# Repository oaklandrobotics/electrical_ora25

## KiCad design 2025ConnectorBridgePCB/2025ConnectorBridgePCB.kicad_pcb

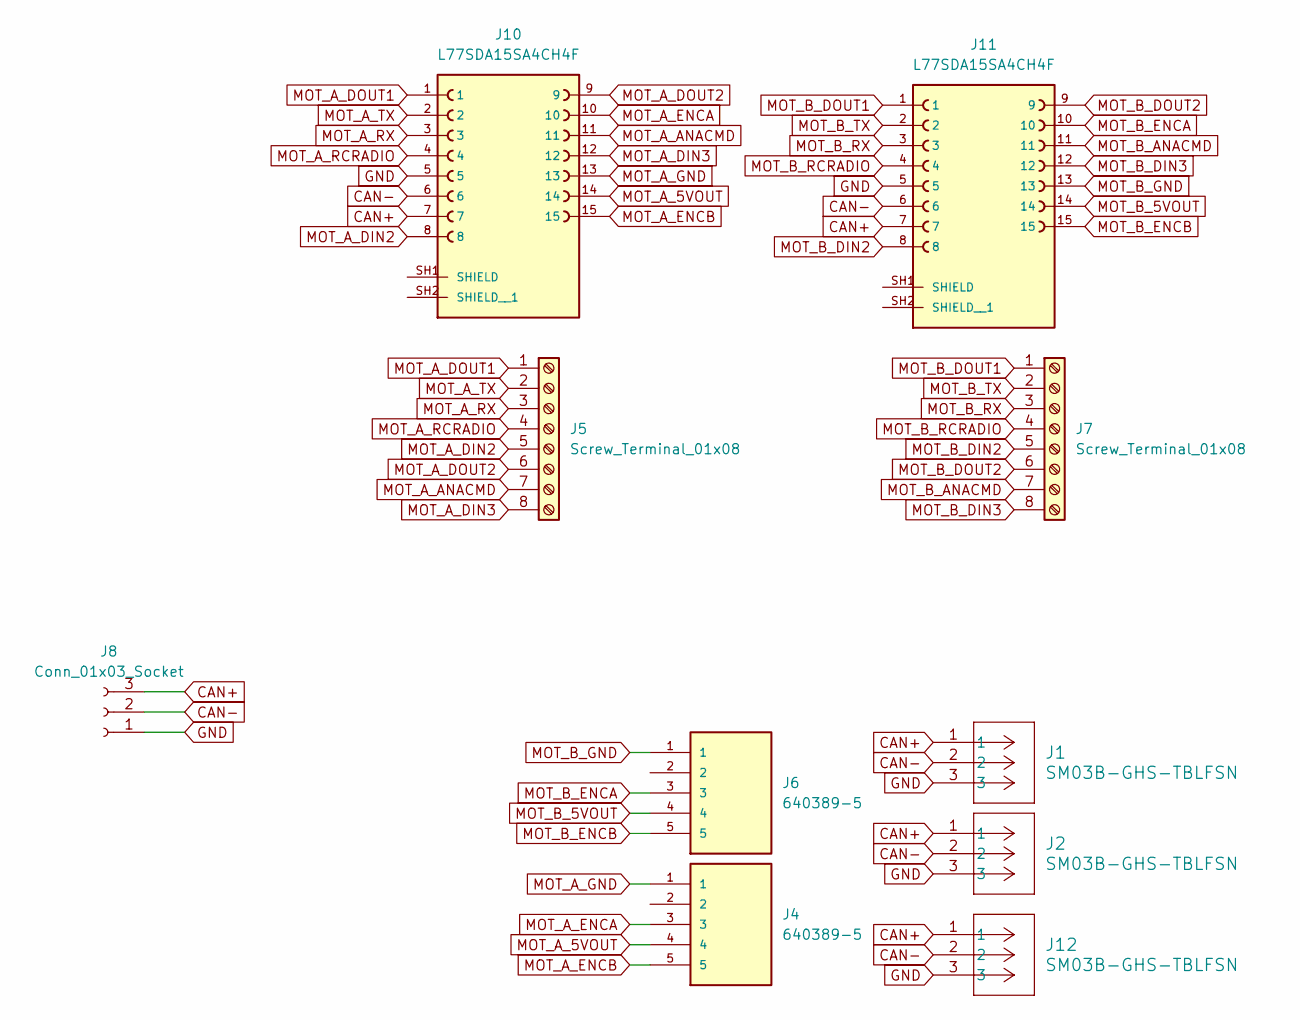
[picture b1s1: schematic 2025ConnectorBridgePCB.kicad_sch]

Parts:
J1, J2, J12: SM03B-GHS-TBLFSN; CONN_SM03B-GHS-TBLFSN_JST
J4, J6: 640389-5; TE_640389-5; PARTREV R; DigiKey_Part_Number A19921-ND
J5, J7: Screw_Terminal_01x08; TerminalBlock_Phoenix_MKDS-1,5-8_1x08_P5.00mm_Horizontal
J8: Conn_01x03_Socket; SolderWire-0.25sqmm_1x03_P4.2mm_D0.65mm_OD1.7mm
J10, J11: L77SDA15SA4CH4F; AMPHENOL_L77SDA15SA4CH4F; PARTREV 3

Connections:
CAN+: J1.1, J2.1, J8.3, J10.7, J11.7, J12.1
CAN-: J1.2, J2.2, J8.2, J10.6, J11.6, J12.2
GND: J1.3, J2.3, J8.1, J10.5, J11.5, J12.3
MOT_A_5VOUT: J4.4, J10.14
MOT_A_ANACMD: J5.7, J10.11
MOT_A_DIN2: J5.5, J10.8
MOT_A_DIN3: J5.8, J10.12
MOT_A_DOUT1: J5.1, J10.1
MOT_A_DOUT2: J5.6, J10.9
MOT_A_ENCA: J4.3, J10.10
MOT_A_ENCB: J4.5, J10.15
MOT_A_GND: J4.1, J10.13
MOT_A_RCRADIO: J5.4, J10.4
MOT_A_RX: J5.3, J10.3
MOT_A_TX: J5.2, J10.2
MOT_B_5VOUT: J6.4, J11.14
MOT_B_ANACMD: J7.7, J11.11
MOT_B_DIN2: J7.5, J11.8
MOT_B_DIN3: J7.8, J11.12
MOT_B_DOUT1: J7.1, J11.1
MOT_B_DOUT2: J7.6, J11.9
MOT_B_ENCA: J6.3, J11.10
MOT_B_ENCB: J6.5, J11.15
MOT_B_GND: J6.1, J11.13
MOT_B_RCRADIO: J7.4, J11.4
MOT_B_RX: J7.3, J11.3
MOT_B_TX: J7.2, J11.2

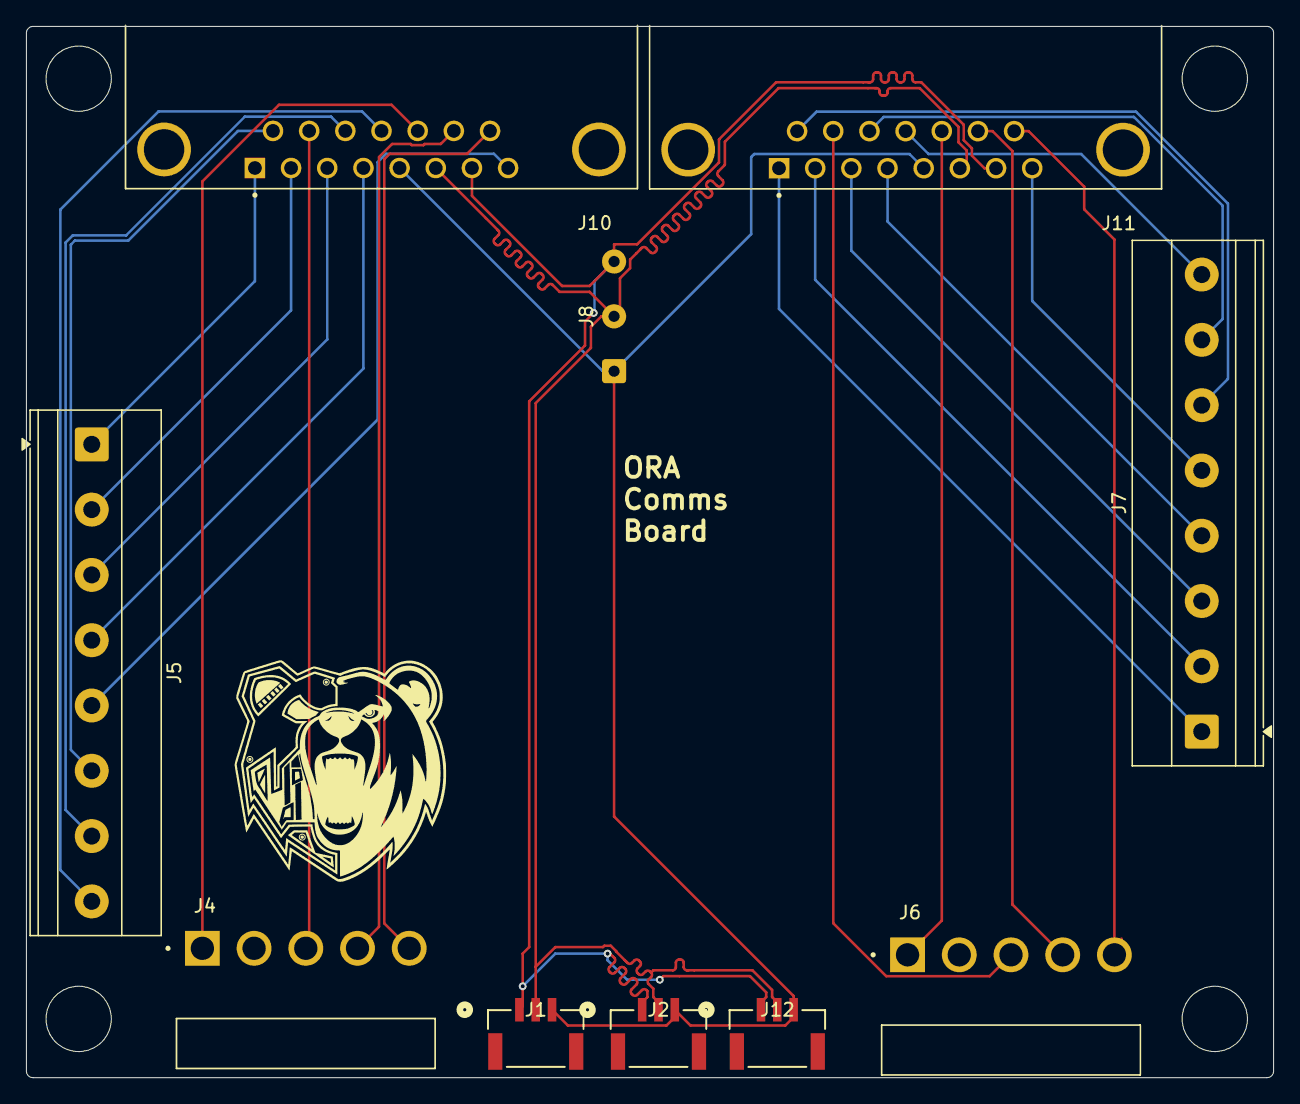
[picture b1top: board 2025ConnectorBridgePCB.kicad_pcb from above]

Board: 2 copper layers, 95.5 x 80.5 mm, 10 parts (0 on the bottom side), 27 nets.

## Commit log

2026-01-26 Add Communication PCB files
    very rough right now, but has traces for DB-15, Encoder, and JST3 CAN setup. MCP2515 and USB might be changed around a bit.
2026-01-27 Replace USB/MCP2515 with daughter board thru hole idea
    We were discussing at one point soldering on a daughter board that houses USB CAN functionality. We can make a branch for onboard USB-CAN functionality
2026-01-28 Shrink Everything, Use proper Encoder Connectors
    This also adds a screw terminal, not wired up yet but it will breakout unused pins from DB15.
2026-02-06 Proper connectors
    Use proper connectors for CAN, Encoders, and DB-15. Breakout unused DB-15 pads to screw terminals.
    Also added mounting holes but did not fillet corners yet in case dimensions need to be changed.
2026-02-06 Comm Board: Fix Missing Connection
2026-02-10 Comm Board: Push Latest Changes
    Moved text back onto board, updated some traces.
2026-03-06 Comm Board: Fix MOT_B_ENCB and CAN line
2026-03-21 Remote EStop: Begin Scaffolding
    Exact communication protocol is WIP but essentially it will be something similar to this.
2026-03-31 Remote EStop: Update last write time for sending module
2026-03-31 Comm Board: Add changes from George
    Added Ground Plane and moved text to silkscreen. Added ORA logo to silkscreen as well.
2026-04-29 Added ESP IMU Board.
2026-05-02 Modifications before ordering. Board is ordered
